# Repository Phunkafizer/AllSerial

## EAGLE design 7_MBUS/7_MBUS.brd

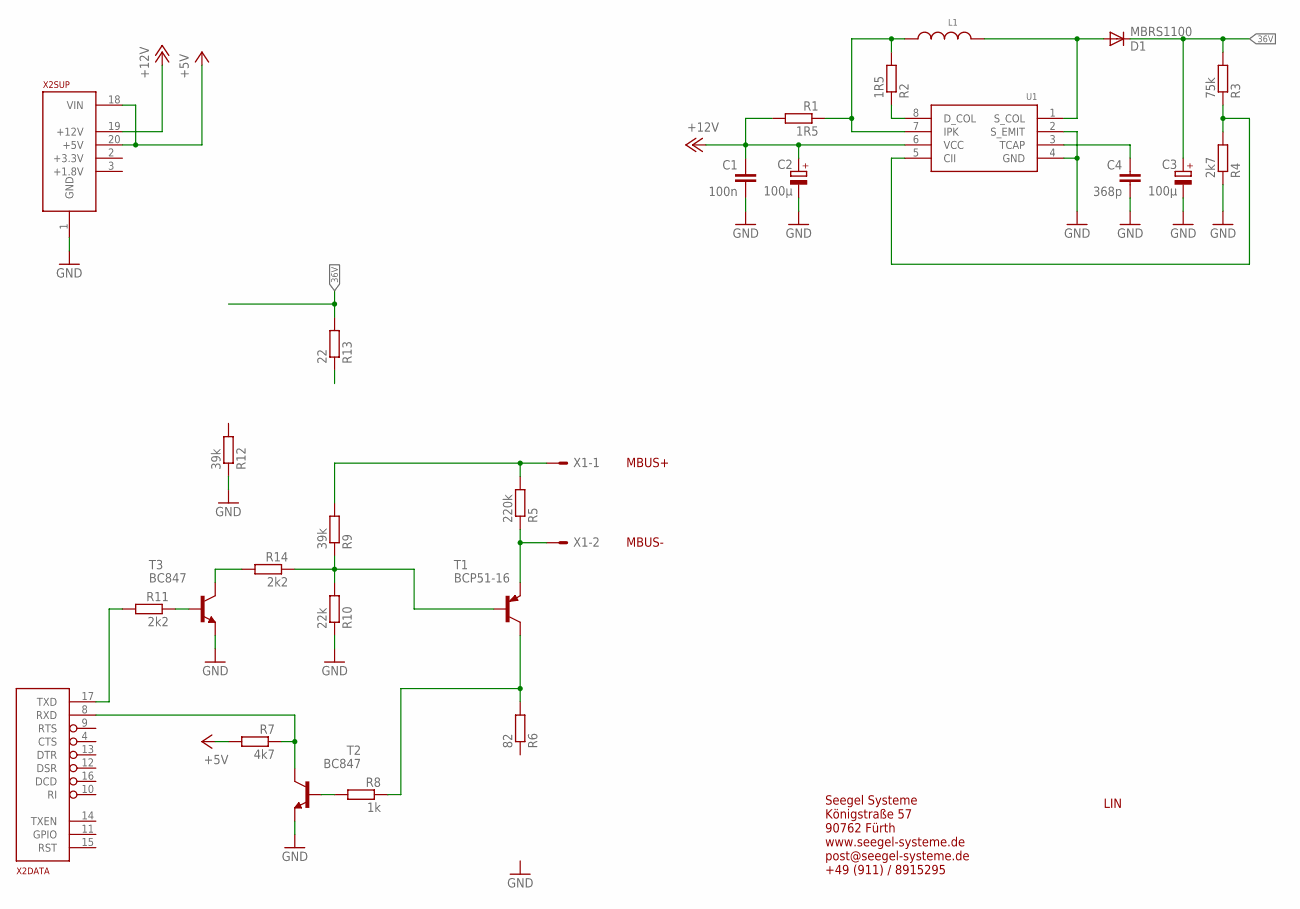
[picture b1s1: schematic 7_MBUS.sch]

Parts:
C1: 100n; C0805
C2, C3: 100µ; PANASONIC_D
C4: 368p; C0805
D1: MBRS1100; DO214AA
L1: WE-PD_1260_74477126; WE-PD_1260/1245/1280/1210
R1, R2: 1R5; R0805
R3: 75k; R0805
R4: 2k7; R0805
R5: 220k; R0805
R6: 82; R0805
R7: 4k7; R0805
R8: 1k; R0805
R9, R12: 39k; R0805
R10: 22k; R0805
R11, R14: 2k2; R0805
R13: 22; R0805
T1: BCP51-16; SOT223
T2, T3: BC847; SOT23
U1: MC34063A; SOIC8_150MIL
X1: AKL18X-02W; AKL182-02
X2: ALLSERIALSLAVE; DAUGHTER-THT

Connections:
36V: C3.+, D1.C, R3.2, R13.2
+5V: R7.2, X2.18 (VIN), X2.20 (+5V)
+12V: C1.1, C2.+, R1.2, U1.6 (VCC), X2.19 (+12V)
GND: C1.2, C2.-, C3.-, C4.2, R4.1, R10.1, R12.1, T2.2 (E), T3.2 (E), U1.2 (S_EMIT), U1.4 (GND), X2.1 (GND)
unnamed: D1.A, L1.1, U1.1 (S_COL)
unnamed: L1.2, R1.1, R2.2, U1.7 (IPK)
unnamed: R2.1, U1.8 (D_COL)
unnamed: R6.2, R8.1, T1.2 (C), T1.4 (C)
unnamed: C4.1, U1.3 (TCAP)
unnamed: R3.1, R4.2, U1.5 (CII)
unnamed: R5.1, T1.3 (E), X1.P$2
unnamed: R11.2, X2.17 (TXD)
unnamed: R7.1, T2.3 (C), X2.8 (RXD)
unnamed: R8.2, T2.1 (B)
unnamed: R9.1, R10.2, R14.1, T1.1 (B)
unnamed: R11.1, T3.1 (B)
unnamed: R14.2, T3.3 (C)
unnamed: R5.2, R9.2, X1.P$1

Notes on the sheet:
LIN
MBUS+
MBUS-
Seegel Systeme Königstraße 57 90762 Fürth www.seegel-systeme.de post@seegel-systeme.de +49 (911) / 8915295

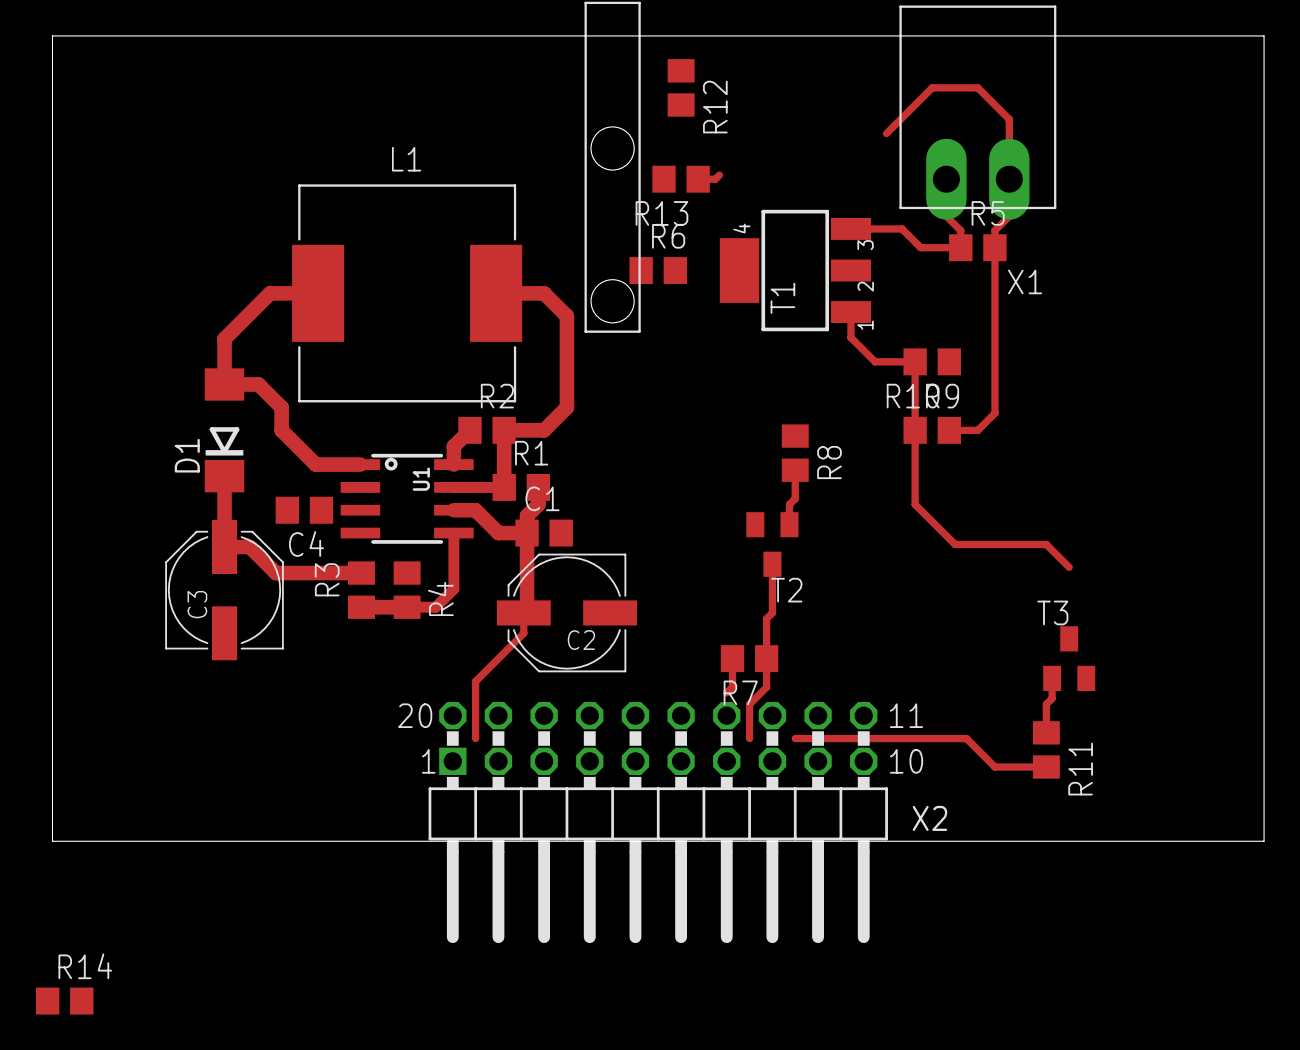
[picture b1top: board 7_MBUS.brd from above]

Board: 2 copper layers, 67.4 x 44.8 mm, 27 parts (0 on the bottom side), 18 nets.

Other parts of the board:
U$1: 1271.1000

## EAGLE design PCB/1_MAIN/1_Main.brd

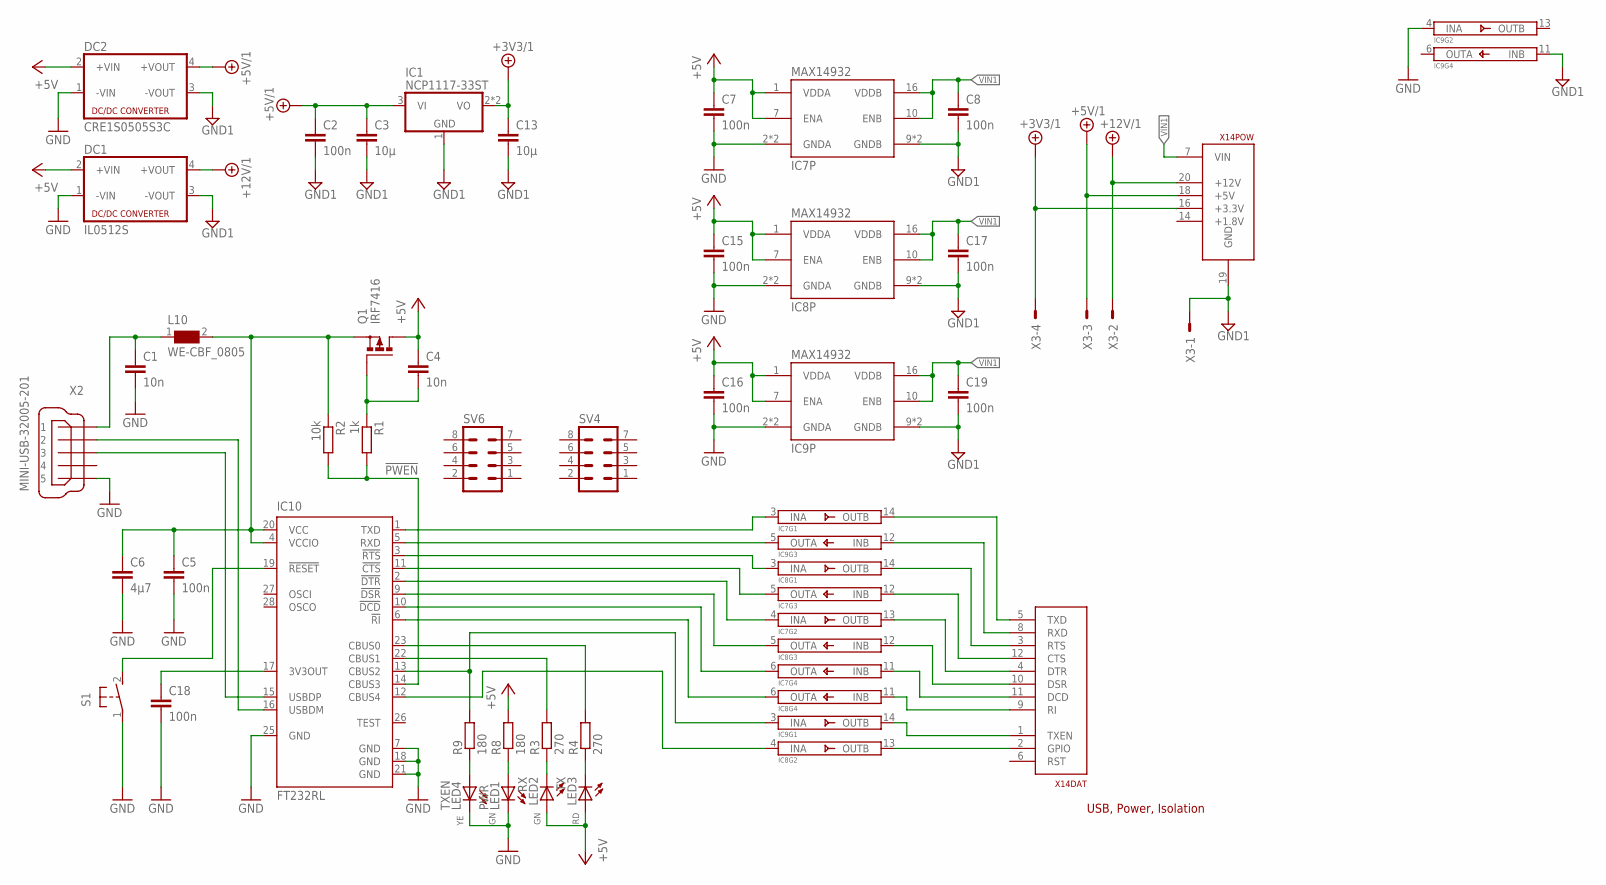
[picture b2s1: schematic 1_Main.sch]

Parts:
C1, C4: 10n; C0805
C2, C5, C7, C8, C15, C16, C17, C18, C19: 100n; C0805
C3, C13: 10µ; C0805
C6: 4µ7; C0805
DC1: IL0512S; NME
DC2: CRE1S0505S3C; NME
IC1: NCP1117-33ST; SOT223
IC7, IC8, IC9: MAX14932; SO16
IC10: FT232RL; SSOP28
L10: WE-CBF_0805; 0805
LED1: PWR; CHIPLED_0603
LED2: RX; CHIPLED_0603
LED3: TX; CHIPLED_0603
LED4: TXEN; CHIPLED_0603
Q1: IRF7416; SO-08
R1: 1k; R0805
R2: 10k; R0805
R3, R4: 270; R0805
R8, R9: 180; R0805
S1: 31-XX; B3F-31XX
SV4, SV6: MA04-2
X2: MINI-USB-32005-201; 32005-201
X3: AKL18X-04W; AKL182-04
X14: ALLSERIALMM; MAIN-THT

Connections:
!PWEN: IC10.14 (CBUS3), R1.2, R2.2
+3V3/1: C13.1, IC1.2 (VO), IC1.4 (VO), X3.P$4, X14.16 (+3.3V)
+5V: C4.1, C7.1, C15.1, C16.1, DC1.2 (+VIN), DC2.2 (+VIN), IC7.1 (VDDA), IC7.7 (ENA), IC8.1 (VDDA), IC8.7 (ENA), IC9.1 (VDDA), IC9.7 (ENA), LED2.A, LED3.A, Q1.5 (D), Q1.6 (D), Q1.7 (D), Q1.8 (D), R8.2
+5V/1: C2.1, C3.1, DC2.4 (+VOUT), IC1.3 (VI), X3.P$3, X14.18 (+5V)
+12V/1: DC1.4 (+VOUT), X3.P$2, X14.20 (+12V)
GND: C1.2, C5.2, C6.2, C7.2, C15.2, C16.2, C18.2, DC1.1 (-VIN), DC2.1 (-VIN), IC7.2 (GNDA), IC7.8 (GNDA), IC8.2 (GNDA), IC8.8 (GNDA), IC9.2 (GNDA), IC9.4 (INA), IC9.8 (GNDA), IC10.7 (GND), IC10.18 (GND), IC10.21 (GND), IC10.25 (GND), LED1.C, LED4.C, S1.1, X2.5
GND1: C2.2, C3.2, C8.2, C13.2, C17.2, C19.2, DC1.3 (-VOUT), DC2.3 (-VOUT), IC1.1 (GND), IC7.9 (GNDB), IC7.15 (GNDB), IC8.9 (GNDB), IC8.15 (GNDB), IC9.9 (GNDB), IC9.11 (INB), IC9.15 (GNDB), X3.P$1, X14.19 (GND)
unnamed: IC9.3 (INA), IC10.13 (CBUS2), R9.2
unnamed: LED3.C, R4.1
unnamed: IC10.19 (!RESET), S1.2 (S)
unnamed: LED2.C, R3.1
unnamed: LED4.A, R9.1
unnamed: LED1.A, R8.1
unnamed: C1.1, L10.1, X2.1
unnamed: IC8.4 (INA), IC10.12 (CBUS4)
unnamed: IC7.3 (INA), IC10.1 (TXD)
unnamed: IC10.16 (USBDM), X2.2
unnamed: IC9.5 (OUTA), IC10.5 (RXD)
unnamed: IC10.15 (USBDP), X2.3
unnamed: C18.1, IC10.17 (3V3OUT)
unnamed: IC8.3 (INA), IC10.3 (!RTS)
unnamed: IC7.5 (OUTA), IC10.11 (!CTS)
unnamed: IC7.4 (INA), IC10.2 (!DTR)
unnamed: IC8.5 (OUTA), IC10.9 (!DSR)
unnamed: IC7.6 (OUTA), IC10.10 (!DCD)
unnamed: IC8.6 (OUTA), IC10.6 (!RI)
unnamed: C5.1, C6.1, IC10.4 (VCCIO), IC10.20 (VCC), L10.2, Q1.1 (S), Q1.2 (S), Q1.3 (S), R2.1
unnamed: C4.2, Q1.4 (G), R1.1
unnamed: IC7.14 (OUTB), X14.5 (TXD)
unnamed: IC9.12 (INB), X14.8 (RXD)
unnamed: IC8.14 (OUTB), X14.3 (RTS)
unnamed: IC7.12 (INB), X14.12 (CTS)
unnamed: IC7.13 (OUTB), X14.4 (DTR)
unnamed: IC8.12 (INB), X14.10 (DSR)
unnamed: IC7.11 (INB), X14.11 (DCD)
unnamed: IC8.11 (INB), X14.9 (RI)
unnamed: IC9.14 (OUTB), X14.1 (TXEN)
unnamed: IC8.13 (OUTB), X14.2 (GPIO)
RXLED: IC10.22 (CBUS1), R3.2
TXLED: IC10.23 (CBUS0), R4.2
VIN1: C8.1, C17.1, C19.1, IC7.10 (ENB), IC7.16 (VDDB), IC8.10 (ENB), IC8.16 (VDDB), IC9.10 (ENB), IC9.16 (VDDB), X14.7 (VIN)

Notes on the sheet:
USB, Power, Isolation

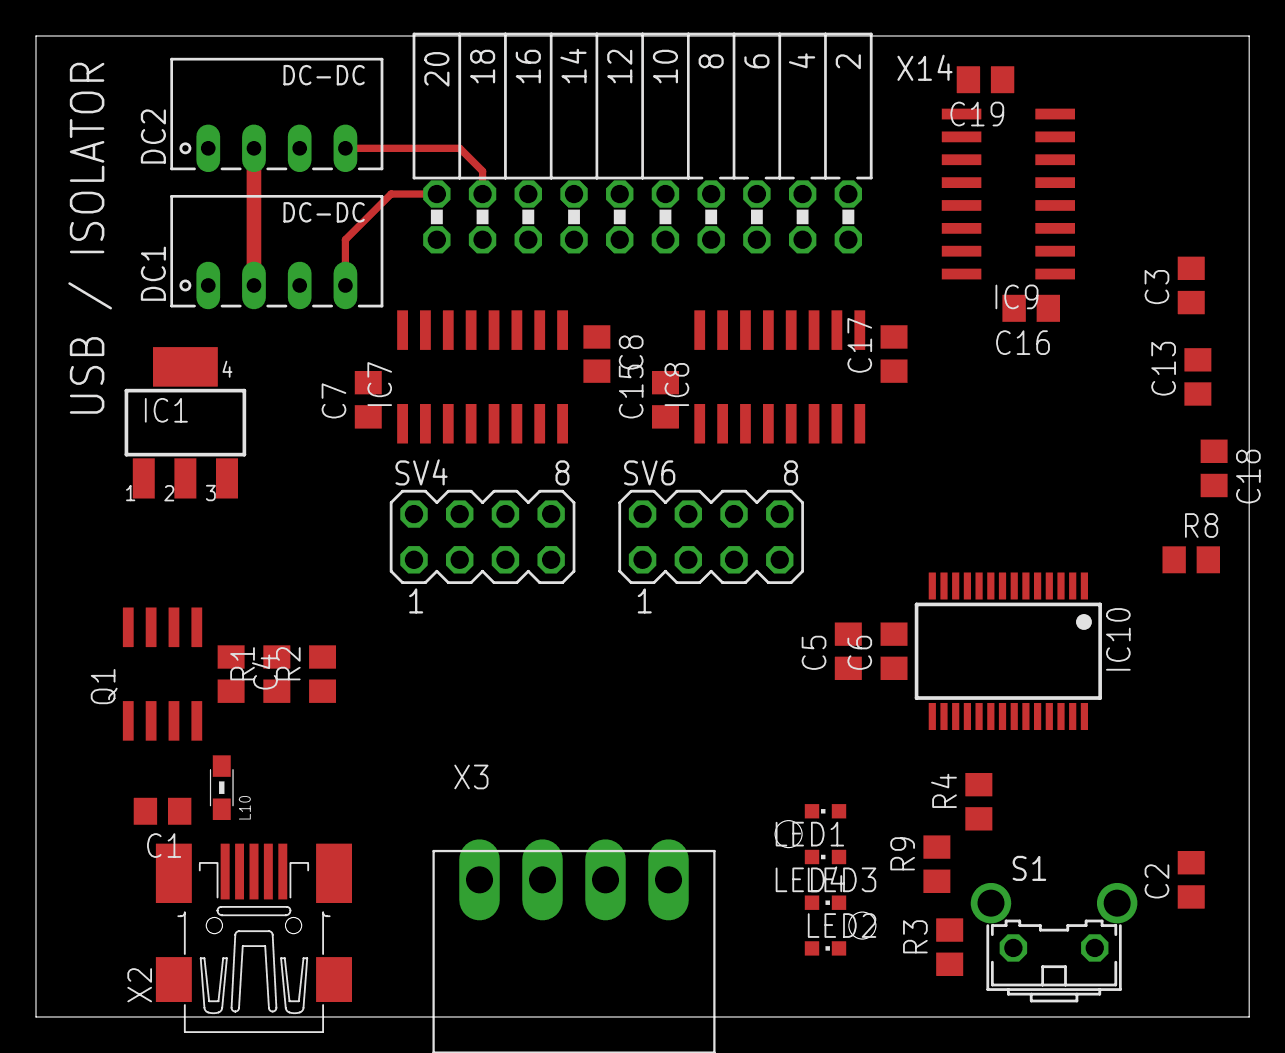
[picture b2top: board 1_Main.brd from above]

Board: 2 copper layers, 67.4 x 54.5 mm, 40 parts (0 on the bottom side), 41 nets.

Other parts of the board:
U$3: 1296.1004

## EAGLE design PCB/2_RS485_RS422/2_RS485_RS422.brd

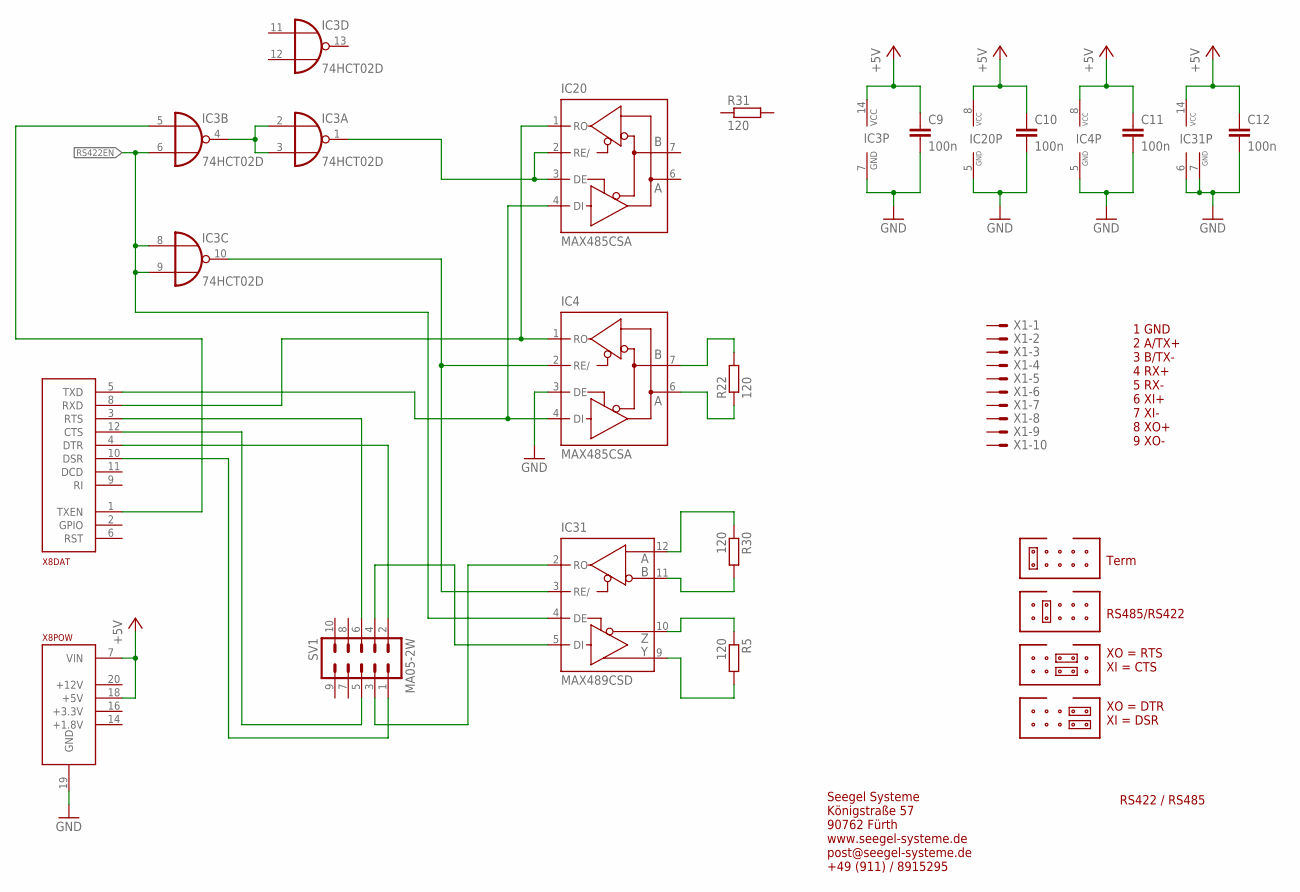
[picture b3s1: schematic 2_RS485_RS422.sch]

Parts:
C9, C10, C11, C12: 100n; C0805
IC3: 74HCT02D; SO14
IC4, IC20: MAX485CSA; SO08
IC31: MAX489CSD; SO14
R5, R22, R30, R31: 120; R0805
SV1: MA05-2W
X1: AKL18X-10W; AKL182-10
X8: ALLSERIALD; DAUGHTER-THT

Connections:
+5V: C9.1, C10.1, C11.1, C12.1, IC3.14 (VCC), IC4.8 (VCC), IC20.8 (VCC), IC31.14 (VCC), X8.7 (VIN), X8.18 (+5V)
GND: C9.2, C10.2, C11.2, C12.2, IC3.7 (GND), IC4.3 (DE), IC4.5 (GND), IC20.5 (GND), IC31.6 (GND), IC31.7 (GND), X8.19 (GND)
unnamed: IC31.11 (B), R30.2
unnamed: IC31.10 (Z), R5.1
unnamed: IC31.9 (Y), R5.2
unnamed: IC3.5 (I0), X8.1 (TXEN)
unnamed: IC31.12 (A), R30.1
unnamed: SV1.5, X8.12 (CTS)
unnamed: IC4.7 (B), R22.2
unnamed: IC4.6 (A), R22.1
unnamed: IC3.2 (I0), IC3.3 (I1), IC3.4 (O)
unnamed: IC3.1 (O), IC20.2 (RE/), IC20.3 (DE)
unnamed: IC3.10 (O), IC4.2 (RE/), IC31.3 (RE/)
unnamed: IC4.1 (RO), IC20.1 (RO), X8.8 (RXD)
unnamed: IC4.4 (DI), IC20.4 (DI), X8.5 (TXD)
unnamed: SV1.6, X8.3 (RTS)
unnamed: SV1.2, X8.4 (DTR)
unnamed: IC31.5 (DI), SV1.4
unnamed: IC31.2 (RO), SV1.3
unnamed: SV1.1, X8.10 (DSR)
RS422EN: IC3.6 (I1), IC3.8 (I0), IC3.9 (I1), IC31.4 (DE)

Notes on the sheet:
Seegel Systeme Königstraße 57 90762 Fürth www.seegel-systeme.de post@seegel-systeme.de +49 (911) / 8915295
RS422 / RS485
Term
RS485/RS422
XO = RTS XI = CTS
XO = DTR XI = DSR
1 GND 2 A/TX+ 3 B/TX- 4 RX+ 5 RX- 6 XI+ 7 XI- 8 XO+ 9 XO-

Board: 2 copper layers, 15 parts (0 on the bottom side), 21 nets, no tracks yet.

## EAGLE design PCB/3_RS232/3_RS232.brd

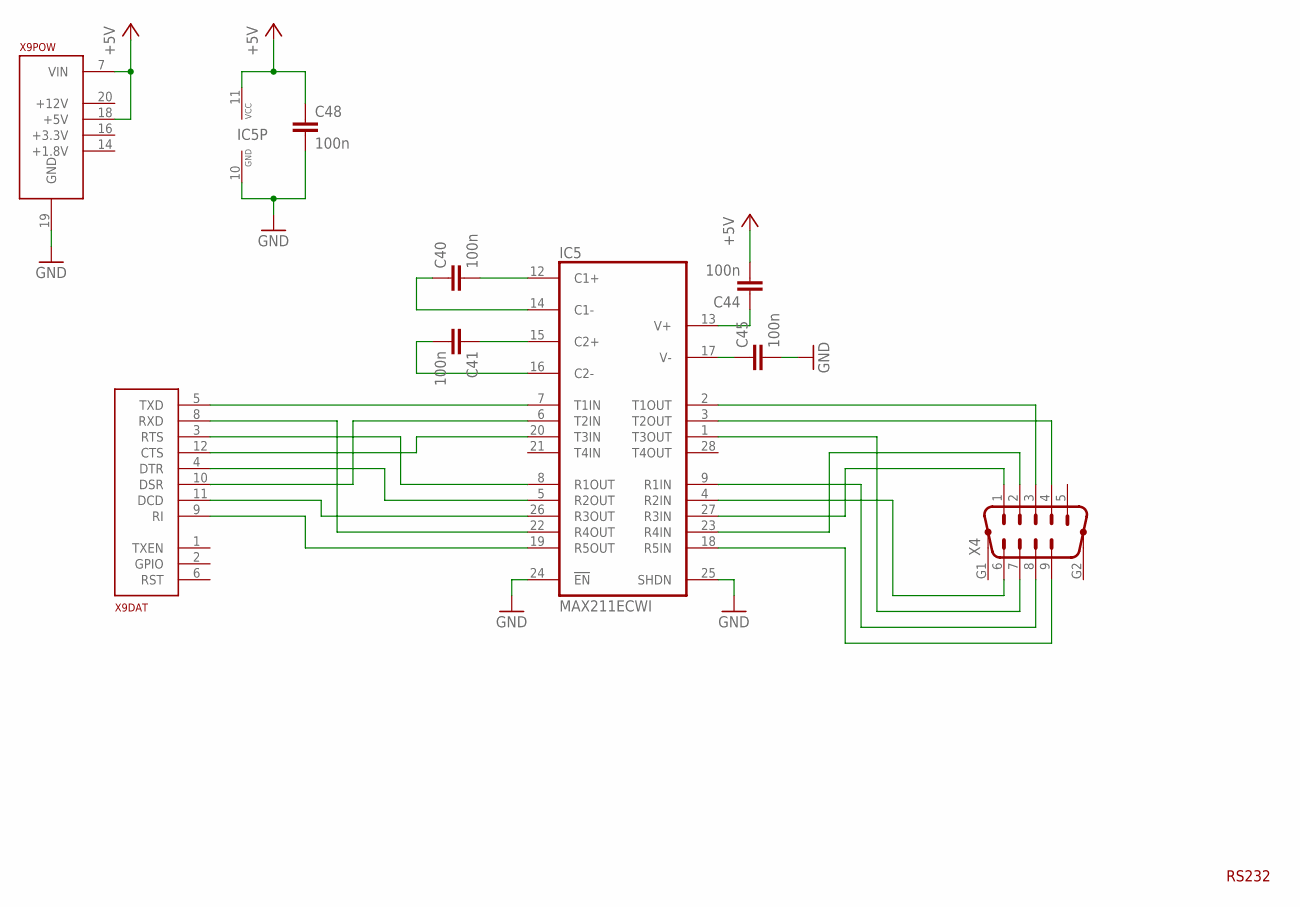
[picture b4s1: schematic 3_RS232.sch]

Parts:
C40, C41, C44, C45, C48: 100n; C0805
IC5: MAX211ECWI; SO28L
X4: M09HP
X9: ALLSERIALD; DAUGHTER-THT

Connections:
+5V: C44.2, C48.1, IC5.11 (VCC), X9.7 (VIN), X9.18 (+5V)
GND: C45.2, C48.2, IC5.10 (GND), IC5.24 (EN), IC5.25 (SHDN), X9.19 (GND)
unnamed: IC5.18 (R5IN), X4.9
unnamed: IC5.9 (R1IN), X4.8
unnamed: IC5.1 (T3OUT), X4.7
unnamed: IC5.4 (R2IN), X4.6
unnamed: IC5.27 (R3IN), X4.1
unnamed: IC5.23 (R4IN), X4.2
unnamed: IC5.2 (T1OUT), X4.3
unnamed: IC5.3 (T2OUT), X4.4
unnamed: C40.2, IC5.12 (C1+)
unnamed: C40.1, IC5.14 (C1-)
unnamed: C41.1, IC5.15 (C2+)
unnamed: C45.1, IC5.17 (V-)
unnamed: C44.1, IC5.13 (V+)
unnamed: C41.2, IC5.16 (C2-)
unnamed: IC5.7 (T1IN), X9.5 (TXD)
unnamed: IC5.22 (R4OUT), X9.8 (RXD)
unnamed: IC5.20 (T3IN), X9.12 (CTS)
unnamed: IC5.8 (R1OUT), X9.3 (RTS)
unnamed: IC5.26 (R3OUT), X9.11 (DCD)
unnamed: IC5.19 (R5OUT), X9.9 (RI)
unnamed: IC5.5 (R2OUT), X9.4 (DTR)
unnamed: IC5.6 (T2IN), X9.10 (DSR)

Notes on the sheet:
RS232

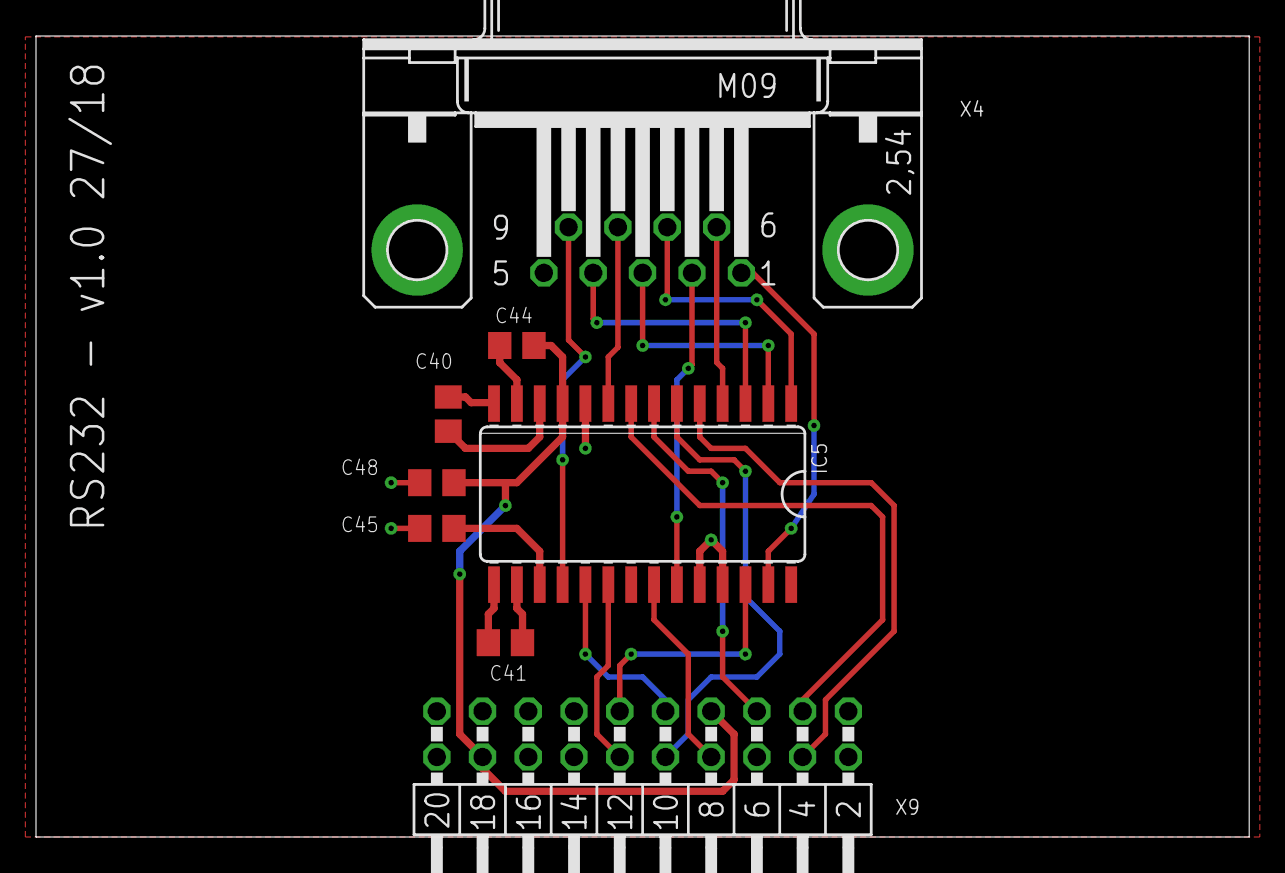
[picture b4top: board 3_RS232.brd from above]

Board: 2 copper layers, 67.4 x 44.5 mm, 8 parts (0 on the bottom side), 24 nets.

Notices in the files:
parts and their libraries:
microbuilder: This work is placed in the public domain, and may be freely used for commercial and non-commercial work with the following conditions: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
PowerMagnetics: Copyright: Würth Elektronik
